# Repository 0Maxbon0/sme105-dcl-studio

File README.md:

# EscortScope — Ford Escort diagnostics by Basita

**An independent Android + ESP32 research platform for exploring legacy Ford EEC-IV diagnostics—carefully, reproducibly, and with raw evidence.**

Built around a **1998 European Ford Escort 1.6 Zetec-E** and an **EEC-IV SME-105** PCM (engineering number `97AB-12A650-KA`). The methodology, transport engineering and test tooling are intended to be useful beyond this particular vehicle.

**[Engineering brief](docs/ENGINEERING_BRIEF.md)** · [Architecture](docs/ARCHITECTURE.md) · [Hardware and components](docs/HARDWARE_GUIDE.md) · [How the code works](docs/CODE_WALKTHROUGH.md) · [Quick start](#get-started-without-a-vehicle) · [Documentation index](docs/README.md)

> [!IMPORTANT]
> **Experimental engineering project—not a certified diagnostic tool.** Network and isolated bench demonstrations do not prove vehicle-bus electrical compatibility, ECU command acceptance, sensor identities, actuator safety or road-use readiness. Do not operate the app while driving. This project is independently developed and **is not affiliated with, endorsed by or supported by Ford Motor Company**.

## Why this project exists

Many older EEC-IV vehicles have limited support in modern diagnostic ecosystems. Command formats, PID meanings and ECU calibration details can vary. A plausible-looking value is not the same as a verified sensor reading.

EscortScope, developed by Basita, is an effort to build a transparent chain from **raw bytes → timestamped capture → reproducible parser → evidence-qualified interpretation**. Rather than treating reverse-engineering hypotheses as established manufacturer specifications, each finding is labeled *Observed*, *Reference*, *Inferred* or *Unknown*.

**Identity:** an independent automotive product by Basita (بسيطة), with a steel-blue automotive action/vehicle identity, official Basita Canvas/Ink surfaces, Lagoon/Mineral selection colors, typography, spacing, controls, semantic colors and motion. See [identity and migration notes](docs/BRANDING_RELEASE.md).

### What it demonstrates

| Engineering area | Implemented work |
| --- | --- |
| **Embedded / real-time** | ESP32 UART bridge, MAX487 interface, time-bounded transmission gates, raw telemetry ring and bounded replay |
| **Android / networking** | Native Capacitor application, local-only WPA2 SoftAP, authenticated TCP, heartbeat and reconnect lifecycle; separate BLE build |
| **Data reliability** | IndexedDB raw archive, sequence-aware RX/RXB, duplicate suppression, inclusive loss reporting and crash recovery |
| **Protocol research** | Ford EEC-IV DCL experiments, Python capture tools, host simulation, and testable candidate sensor conversions |
| **Testing / engineering discipline** | Node.js, Python, JVM and PlatformIO checks, safety invariants and documented hardware-vs-simulation boundaries |

## Application preview

<table>
  <tr>
    <td align="center"></td>
    <td align="center"></td>
  </tr>
  <tr><td align="center"><sub>Live telemetry view</sub></td><td align="center"><sub>Captured-data replay view</sub></td></tr>
</table>

*These are historical application screenshots, not a claim that the latest build or every displayed sensor mapping has been validated on a vehicle.*

## Current engineering status

**Current release (26 November 2026):** Android **v2.2.1** (build **31**) and ESP32 firmware **v30**. EscortScope was installed in place on a Samsung Galaxy A52s; the original package identity and saved recordings were retained. The compact live dashboard exposes readings earlier and offers direct data-set selection. All application select lists now use the branded choice sheet; saved readings use grouped dates, search and Complete/Incomplete filters. Failed and empty captures remain in the engineering archive; completion may be annotated manually without changing the diagnostic verdict. The startup screen follows actual initialization and the original Basita Unravel credit loops silently every 7.63 seconds in both themes.

**Physical bridge validation:** v30 BLE was flashed and verified by USB. With the ECU disconnected, the phone completed TX2 self-test and reached the initial DCL transmission. The former v29 BLE output reservation could never fit in its 4 KiB queue. v30 reserves a bounded report in an 8 KiB queue without bypassing electrical safety gates. Vehicle ECU response remains unverified.

**Software checks:** see the [current release notes](docs/BRANDING_RELEASE.md), [developer setup](docs/DEVELOPER_SETUP.md) and [GitHub Actions CI](.github/workflows/ci.yml). Both ESP32 profiles compiled; Android debug assembly and in-place installation passed. The earlier November 9 Wi-Fi demonstration and November 11 recovery verification remain historical observations, not current on-vehicle acceptance.

| Capability | Evidence level / limitation |
| --- | --- |
| Direct Android ↔ ESP32 Wi-Fi | **Bench demonstrated** on 9 November 2026; no router or Internet required |
| Live Data reconnect/resume | **Host-tested**; hardware RF/thermal soak and on-vehicle behavior not yet established for the new implementation |
| Recovery grace | Up to **30 s** to reconnect; not a promise of 30 s lossless telemetry |
| Telemetry history | **8,000 × 5 bytes** of raw events; ~8.3 s at a continuous 960-byte/s stream, longer at lower rates |
| EEC-IV commands, sensors and scaling | **Research in progress**; target-ECU mappings require independent confirmation |
| High-idle / VSS investigation | [Diagnostic hypotheses and validation limits](docs/high-idle-diagnosis.md), **not a confirmed ECU defect** |

A dated [physical direct-link bench report](docs/releases/2026-11-09-direct-softap-bench.md) documents the previously observed bridge connection. It must not be mistaken for field validation of the subsequent November 11 recovery changes.

## Architecture

```text
Android app (Capacitor / JavaScript / IndexedDB)
    │ Native Android Wi-Fi NetworkSpecifier + WPA2
    │ Local-only TCP :8765, session authentication
    ▼
ESP32 SoftAP (10.77.13.1 / default SSID: SME105-DIRECT-2BF8)
    │ Wi-Fi and BLE are separate firmware profiles
    │ Heartbeat, 30 s retained-session grace, bounded RX replay
    ▼
ESP32 EEC-IV DCL bridge firmware (PlatformIO, v30)
    │ USB serial for trusted provisioning and bench diagnostics
    │ Explicit per-boot TX2_BENCH + ARM/READ gates
    ▼
MAX487 electrical interface → vehicle DCL bus
    ONLY after separate electrical and procedural qualification
```

Network authentication uses an owner-entered WPA2 passphrase and its SSID-bound PBKDF2-derived session token. This is **one shared secret**, not two independent authentication factors. On Android, private credential handling uses Keystore-backed storage. No vehicle transmission occurs merely because a device connects or reconnects.

See [full architecture](docs/ARCHITECTURE.md), [Wi-Fi setup](docs/wifi_bridge_architecture_and_setup.md), [wiring and electrical safety](docs/wiring-safety.md), [code walkthrough](docs/CODE_WALKTHROUGH.md), and [firmware overview](firmware/README.md).

## Hardware — assembled bridge vs. PCB concepts

The current research bridge uses an **ESP32 DevKit-class board**, **5 V MAX487 transceiver**, receive-line **5 V → 3.3 V translation**, hardware **DE pull-down**, and USB/separately protected bench power. This is different from the **KiCad PCB R0 and compact R1** designs. R1 is a 95 × 60 mm, four-layer **review-only design** with provisional automotive power protection, regulator choices and an ESP32-WROOM-32UE module. It has **not been fabricated or vehicle-qualified**.

[Parts, GPIO map and connector caveats](docs/HARDWARE_GUIDE.md) · [KiCad design workspace](hardware/README.md) · [R1 review status](hardware/pcb-r1/REVIEW_STATUS.md)

*PCB visual is a design preview only. Passing ERC/DRC does not make a board safe to connect to an ECU.*

## Get started without a vehicle

The fastest useful evaluation is **software-only**: clone the repository, execute parsers/tests and examine the source. **You do not need an ECU, car, connected ESP32 or private diagnostic captures** for the public baseline tests (capture-dependent tests may skip).

### Requirements

- Node.js **22** and npm
- Python **3.12+** for the documented development/test environment
- Optional: JDK **21** and Android SDK for APK builds
- Optional: PlatformIO and a compatible ESP32 board for firmware development

```bash
git clone https://github.com/0Maxbon0/sme105-dcl-studio.git
cd escort-sme105-diagnostic-lab
npm ci
npm test
python -m pip install -e .
PYTHONPATH=src python -m unittest discover -s tests -q
```

Optional **compile-only** checks (no device flash):

```bash
python -m pip install -e '.[firmware]'
python -m platformio run -d firmware/sme105_usb_bridge -e esp32dev
python -m platformio run -d firmware/sme105_usb_bridge -e esp32dev_ble
```

For Android development:

```bash
npm run android:sync
cd android
./gradlew :app:testDebugUnitTest :app:assembleDebug
```

On Windows, use `gradlew.bat`. The resulting *debug* APK is at `android/app/build/outputs/apk/debug/app-debug.apk`. This README does **not** recommend connecting to the vehicle or installing experimental firmware as a first test. Provisioning and rollback are described separately in [technical setup](docs/wifi_bridge_architecture_and_setup.md).

## Repository guide

| Path | Purpose |
| --- | --- |
| [`app/`](app/) | Canonical Android WebView application and offline UI, **not** an obsolete website |
| [`android/`](android/) | Native Android plugins, transport lifecycle and JVM tests |
| [`firmware/sme105_usb_bridge/`](firmware/sme105_usb_bridge/) | ESP32 Wi-Fi/BLE builds, ring replay and hardware protection |
| [`src/ford_dcl/`](src/ford_dcl/) | Python capture and offline inspection CLI |
| [`tests/`](tests/) / [`app/tests/`](app/tests/) | Host, parser, transport and recovery regression suites |
| [`docs/`](docs/) | Guided docs index, architecture, hardware, research references, experiment logs and safety |
| [`hardware/`](hardware/) | Review-only editable KiCad PCB R0/R1 concepts, separate from the hand-wired prototype |
| [`artifacts/`](artifacts/) | Dated visual/test artifacts, **not** an APK distribution channel |
| [`captures/`](captures/) | Historical research evidence; treat raw samples as potentially sensitive |

The retired Python localhost GUI is not the supported user interface. The Android app's canonical web assets live under `app/`.

## Research integrity and safety

- **Observed** means an explicitly identified raw capture or witnessed bench/vehicle event; **Reference** means a cited external source; **Inferred** means a testable hypothesis; **Unknown** means unverified.
- A recognized command frame is **not** proof that this ECU accepts the command. A decoded PID-like number is **not** proof of its engineering units.
- There is no general arbitrary ECU-byte write API and no automatic transmit on boot, network connection or recovery. Named operations require safety gates and operator authorization. **Do not use this software as a driving aid or to deliberately reproduce an unsafe engine symptom.**
- Do not publish vehicle-identifying information, passwords, Wi-Fi tokens, NVS dumps, phone backups or sensitive recordings. Existing historical captures are preserved; see [security](SECURITY.md) for responsible reporting.

Explore the [protocol notes](docs/protocol-notes.md), [experiment plan](docs/sme105-dcl-experiment-plan-2026-11-07.md), [references](docs/REFERENCES.md) and [high-idle research](docs/high-idle-diagnosis.md).

For an overview of code internals and safe local builds, read [code walkthrough](docs/CODE_WALKTHROUGH.md) and [developer setup](docs/DEVELOPER_SETUP.md). Before sharing the repository externally, use the [publication checklist](docs/PUBLICATION_CHECKLIST.md).

## For Ford / technical reviewers

The [two-page-style engineering brief](docs/ENGINEERING_BRIEF.md) summarizes the problem, implemented architecture, verification levels, unanswered questions and specific requests for historical EEC-IV documentation or calibration information. The project's intent is to improve maintainability and safe understanding of a legacy vehicle, **not** to imply access to or endorsement by Ford engineering.

## Contributing, security and licensing

Reports should include the exact ECU and firmware/app versions, transport mode, safety state, original capture identifier, clock settings, digest and reproduction steps. Keep identifying raw captures private. See the [wiring and electrical safety guide](docs/wiring-safety.md).

Contributions to parsers, tests, documentation and evidence-based research are welcome. Please read [CONTRIBUTING.md](CONTRIBUTING.md) and [SECURITY.md](SECURITY.md) before sharing files or proposing active hardware experiments.

**License status:** This repository is **publicly viewable but not currently open-source licensed**. Public access alone does not grant reuse, modification or redistribution rights. The maintainer must deliberately select and add a license before describing the code as open source.

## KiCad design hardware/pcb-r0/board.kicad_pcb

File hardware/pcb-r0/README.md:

# SME105 DCL Bridge — PCB R0 engineering prototype

**State:** editable KiCad schematic and four-layer PCB now routed with ground planes. Prototype-review **only**: NOT vehicle-qualified, NOT manufacturing approved. See `REVIEW_STATUS.md`.
**Source reviewed:** firmware/sme105_usb_bridge/README.md and platformio.ini; docs/wiring-safety.md, docs/max487-quickstart.md and docs/wifi_ble_stability_and_rf_report.md.
**Scope:** single-board replacement for current ESP32 DevKit + MAX487 + RO 5V-to-3.3V translation; retain the existing GPIO map and firmware. Add protected OBD power and optional external 2.4 GHz antenna. No new Bluetooth chipset needed.

## Electrical architecture — proposed

```text
OBD verified pigtail (J1 header placeholder)  Automotive protection/power
  pin 16 VBAT --- fuse --- reverse-polarity stage --- surge clamp
                                                  |
                                   automotive buck 5V (candidate LM5164-Q1)
                                     |                       |
                                 MAX487 VCC              3V3 regulator
                                     |                       |
OBD pin 3?  -------- DNP link -- A/B?                     ESP32-WROOM-32UE-N4
OBD pin 11? -------- DNP link -- B/A?                       | BLE + Wi-Fi integrated
                                     |                        +-- IPEX 2.4 GHz antenna
                            MAX487 RO -- resistor divider --> GPIO16
                            MAX487 DI <------------------------ GPIO17
                            MAX487 DE <------------------------ GPIO18
                                   + 10k pull-down to GND
                            MAX487 /RE --> GND (receiver enabled)
OBD pin 4 --> GND; pin 5 --> reference-isolation DNP link; verify on car
UART programming/service header: 3V3/GND/TXD0/RXD0/EN/GPIO0 (and optional USB/UART debug adapter)
OBD pin 7 IS NOT DCL; leave unconnected in R0.
```

## Reused firmware signals (confirmed from source)

| Logic | ESP32 GPIO | WROOM-32UE pad | Direction | Other end |
|---|---:|---:|---|---|
| DCL RX | 16 | 27 | IN | MAX487 RO through 5V->3V3 conversion |
| DCL TX | 17 | 28 | OUT and pad witness | MAX487 DI |
| Driver enable | 18 | 30 | OUT | MAX487 DE and 10k resistor to GND |
| Enable receiver | — | — | — | MAX487 /RE tied to GND |
| UART flashing | TXD0/RXD0 | 35/34 | IO | service header; no DevKit USB-UART required |

## Core choices

1. **ESP32-WROOM-32UE-N4** rather than the complete DevKit. The classic ESP32 core retains the GPIO/UART architecture used by the repository; N4 has 4 MB flash. The UE version includes an RF connector for a *suitable* approved 2.4 GHz antenna.
2. **No second Bluetooth module:** current firmware already contains optional NimBLE UART transport (build flag `SME105_BLE`); deployed Wi-Fi image is a different configuration. Improve radio by antenna placement/measurements, not a second radio by assumption.
3. **Keep the existing MAX487 functional interface for R0.** A 3.3V-native replacement could eliminate the 5V RX translator, but changes the bus electrical interface and requires validation against the actual DCL wiring.
4. **Input power is a fresh engineering subsystem, not the old bench wiring.** 12V OBD pin 16 must never connect directly to ESP32/5V/3V3 rails. Proposed protection chain and a 6–100 V-rated automotive buck are preliminary; final reverse polarity, surge/load-dump, fuse, thermal and sleep-current design must be calculated and tested before vehicle power-on.
5. **No assumption that pins 3/11 A/B or 120-ohm termination are correct** until measured on this specific SME-105 ECU and connector.
6. Boot hardware must hold DE OFF regardless of ESP boot state. Reserve access for programming/debugging even after removing the DevKit.

## Suggested PCB zones (mechanical dimensions NOT final)

- **Vehicle-facing edge:** OBD connector, fuse/reverse-polarity/surge input, DCL protection.
- **Center:** 5V/3V3 switching supply, MAX487, RO divider.
- **Antenna edge:** WROOM-32UE with connector and RF clearance; antenna routed away from car metal and switching inductor.
- **Service:** test pads + UART firmware recovery header + optional physical disconnect/disable for bus driver.
- Board shape depends on the exact OBD male connector and case. Do **not** commit to dimensions or component footprints without the mechanical part numbers.

## Release gates (before CAD manufacturing exports)

- Confirm current physical module identity, 5V logic shifter board and MAX487 part/variant; record photographs of both sides.
- Verify exact OBD connector pins and GND, especially DCL 3/11 polarity and actual bus load, on this car.
- Choose direct-plug or short-cable OBD male connector and enclosure dimensions.
- Complete KiCad GUI ERC, resolve 0.20 mm thermal drill feasibility and review PCB copper and antenna layout with real module and manufacturer constraints.
- Validate automotive power path (reverse polarity, cranking, load dump/transients, peak Wi-Fi/BLE current, ignition-off parasitic drain).
- Compare USB-only bench functional signals and active-driver safety with existing bridge; field ECU operation is a separate approval.
- Compile and verify matching Wi-Fi and BLE profiles on the replacement module without altering saved app/device settings unexpectedly.

## Primary component references

- Espressif ESP32-WROOM-32E/32UE datasheet: https://documentation.espressif.com/esp32-wroom-32e_esp32-wroom-32ue_datasheet_en.html
- Espressif ESP32 hardware schematic checklist: https://docs.espressif.com/projects/esp-hardware-design-guidelines/en/latest/esp32/schematic-checklist.html
- TI LM5164-Q1 candidate regulator: https://www.ti.com/product/LM5164-Q1
- KiCad: https://www.kicad.org/

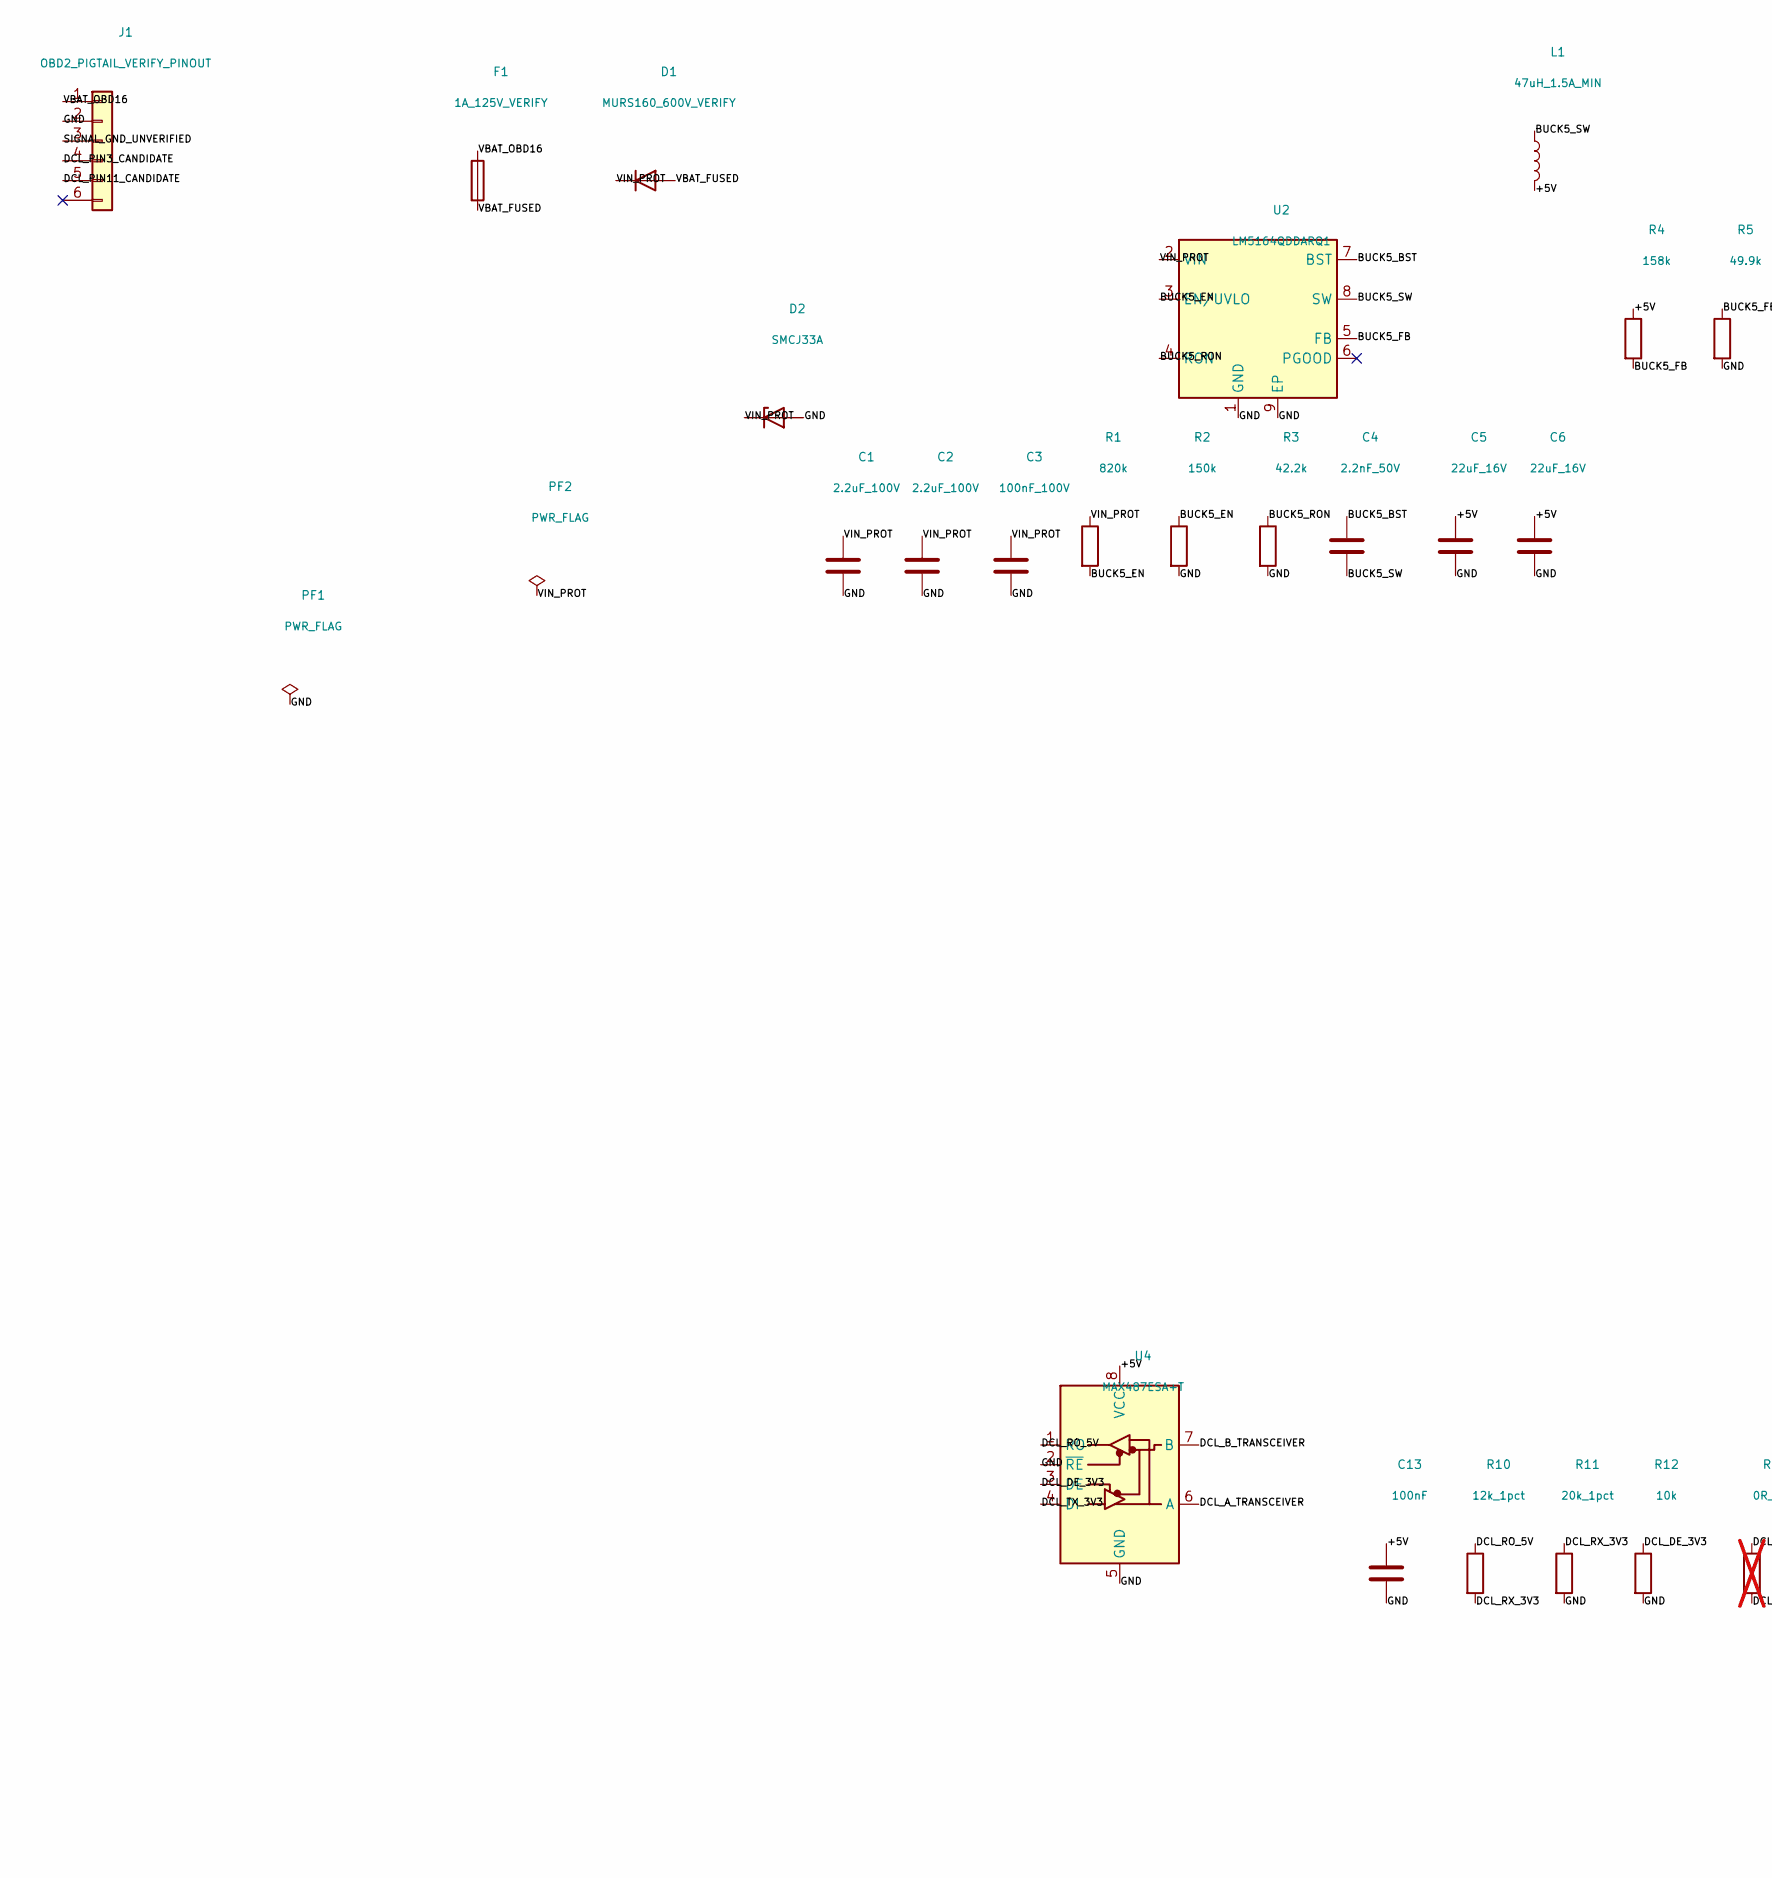
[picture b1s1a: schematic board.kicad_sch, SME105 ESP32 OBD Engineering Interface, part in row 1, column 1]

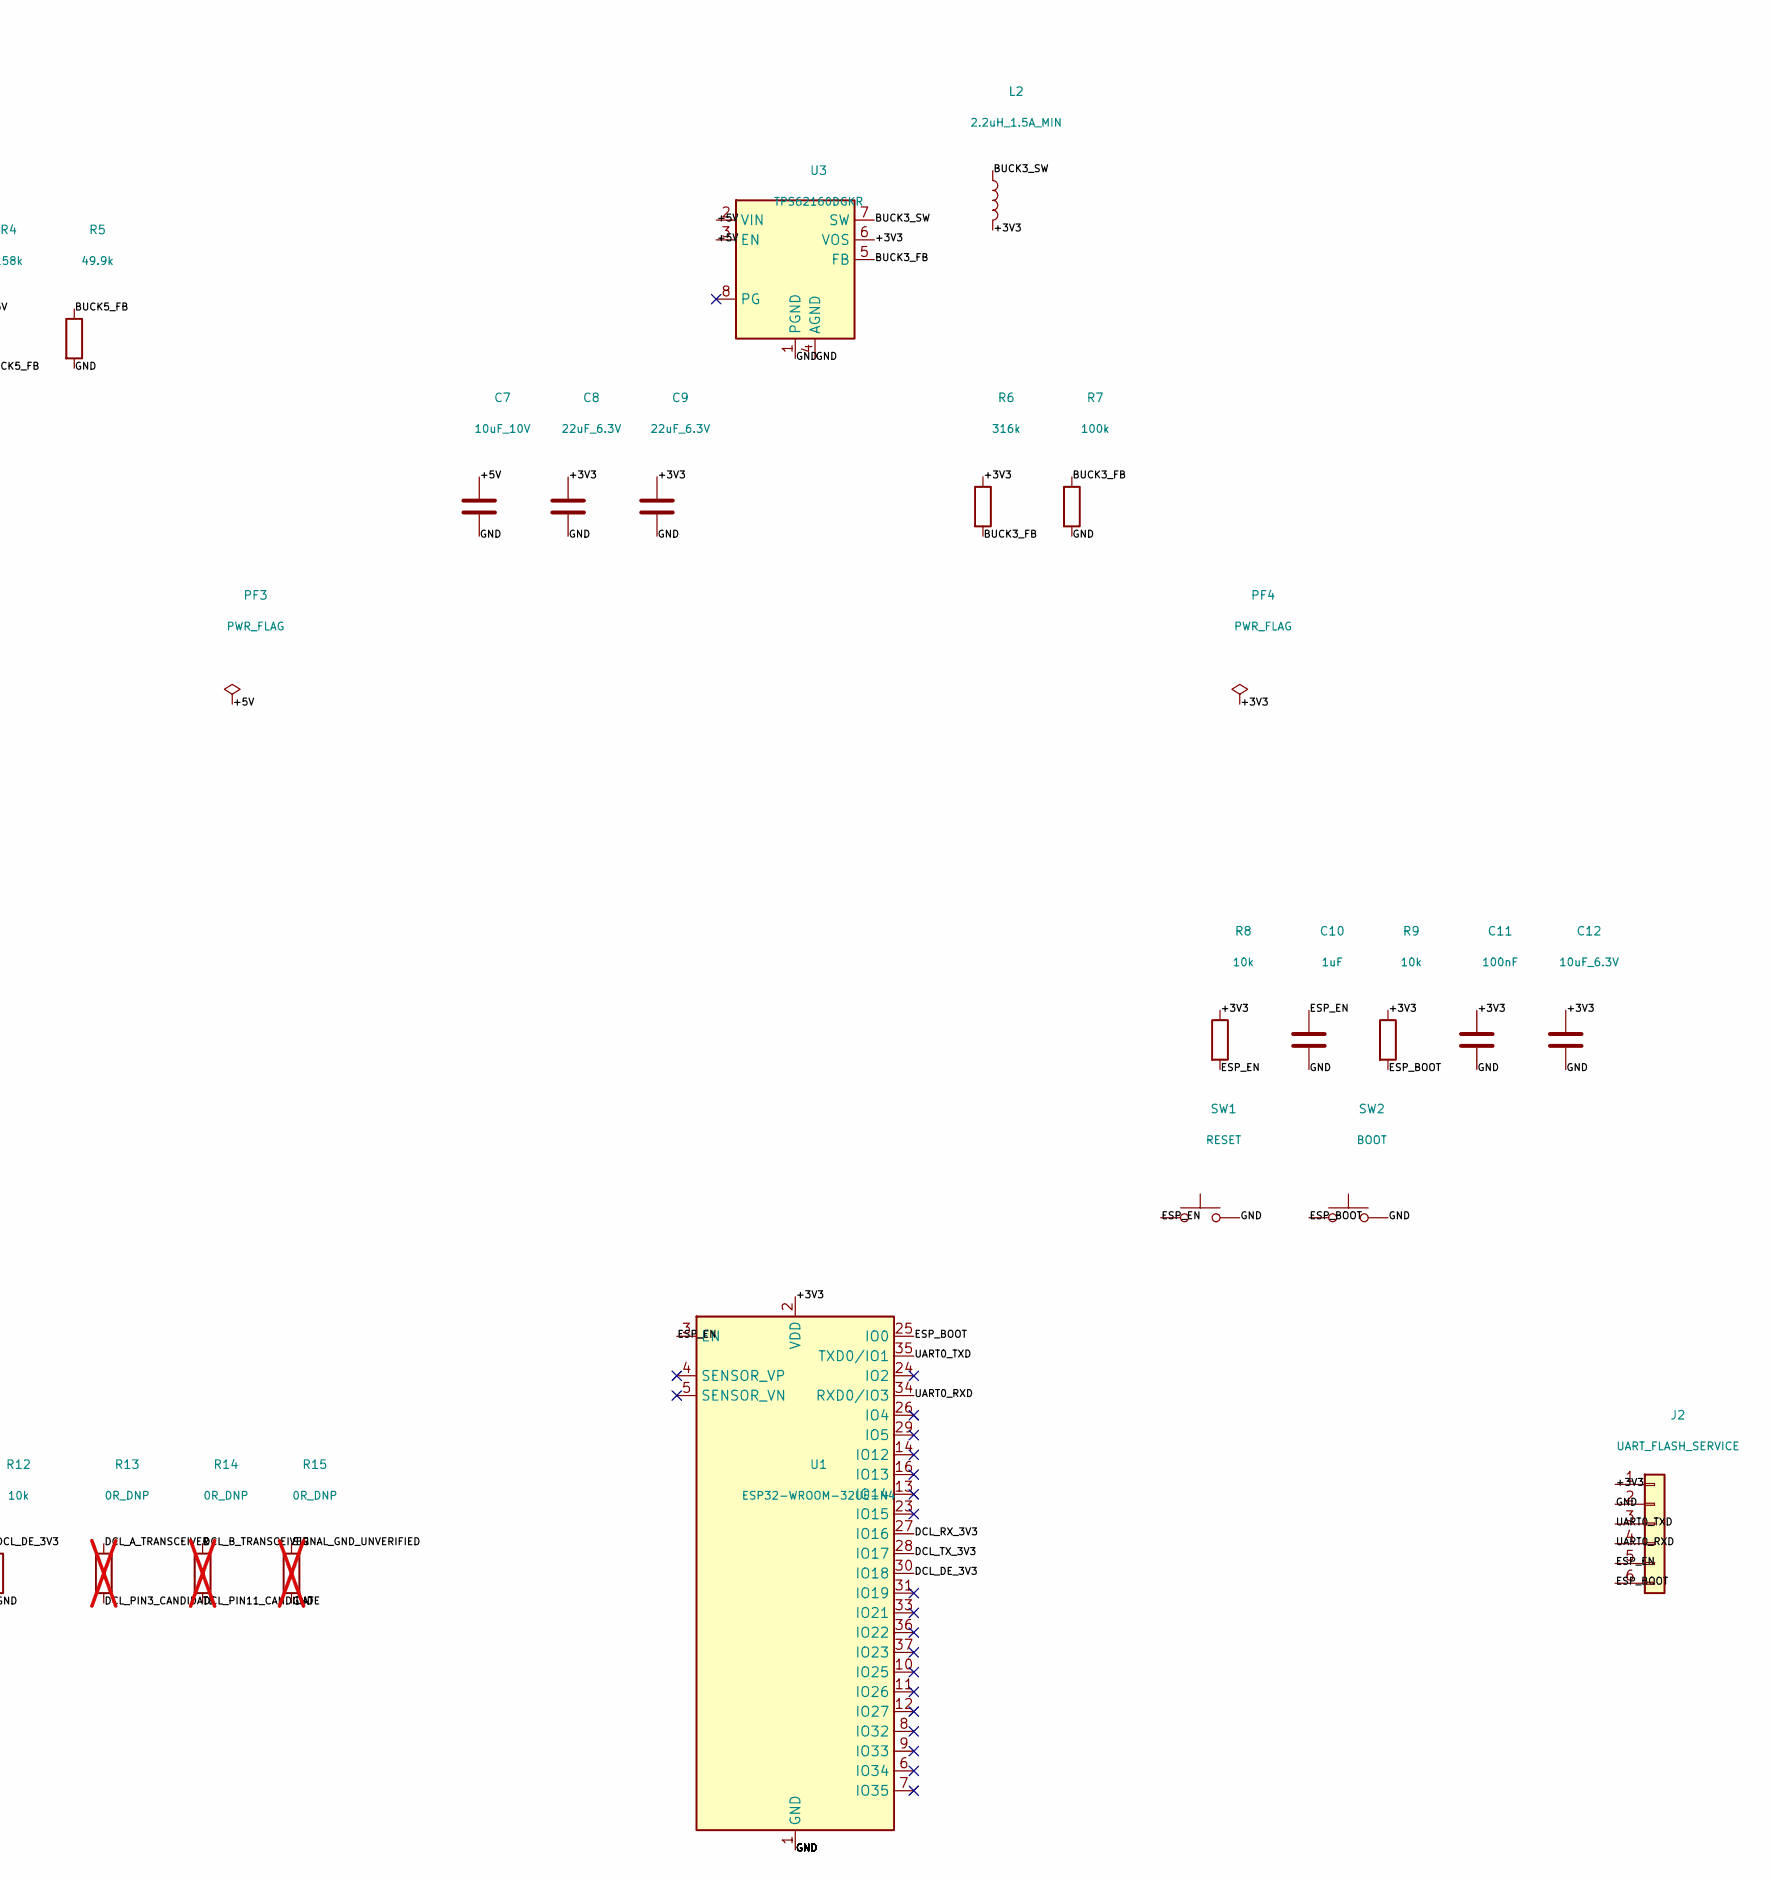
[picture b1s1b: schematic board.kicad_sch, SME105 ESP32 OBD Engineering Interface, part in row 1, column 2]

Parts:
C1, C2: 2.2uF_100V; Capacitor_SMD__C_1210_3225Metric
C3: 100nF_100V; Capacitor_SMD__C_0805_2012Metric
C4: 2.2nF_50V; Capacitor_SMD__C_0603_1608Metric
C5, C6: 22uF_16V; Capacitor_SMD__C_1206_3216Metric
C7: 10uF_10V; Capacitor_SMD__C_1206_3216Metric
C8, C9: 22uF_6.3V; Capacitor_SMD__C_1206_3216Metric
C10: 1uF; Capacitor_SMD__C_0603_1608Metric
C11, C13: 100nF; Capacitor_SMD__C_0603_1608Metric
C12: 10uF_6.3V; Capacitor_SMD__C_1206_3216Metric
D1: MURS160_600V_VERIFY; Diode_SMD__D_SMB
D2: SMCJ33A; Diode_SMD__D_SMC
F1: 1A_125V_VERIFY; Fuse__Fuse_2512_6332Metric
J1: OBD2_PIGTAIL_VERIFY_PINOUT; Connector_PinHeader_2.54mm__PinHeader_1x06_P2.54mm_Vertical
J2: UART_FLASH_SERVICE; Connector_PinHeader_2.54mm__PinHeader_1x06_P2.54mm_Vertical
L1: 47uH_1.5A_MIN; Inductor_SMD__L_10.4x10.4_H4.8
L2: 2.2uH_1.5A_MIN; Inductor_SMD__L_Taiyo-Yuden_NR-50xx
PF1, PF2, PF3, PF4: PWR_FLAG
R1: 820k; Resistor_SMD__R_0603_1608Metric
R2: 150k; Resistor_SMD__R_0603_1608Metric
R3: 42.2k; Resistor_SMD__R_0603_1608Metric
R4: 158k; Resistor_SMD__R_0603_1608Metric
R5: 49.9k; Resistor_SMD__R_0603_1608Metric
R6: 316k; Resistor_SMD__R_0603_1608Metric
R7: 100k; Resistor_SMD__R_0603_1608Metric
R8, R9, R12: 10k; Resistor_SMD__R_0603_1608Metric
R10: 12k_1pct; Resistor_SMD__R_0603_1608Metric
R11: 20k_1pct; Resistor_SMD__R_0603_1608Metric
R13, R14, R15: 0R_DNP; Resistor_SMD__R_0805_2012Metric; not fitted
SW1: RESET; Button_Switch_SMD__SW_SPST_B3U-1000P
SW2: BOOT; Button_Switch_SMD__SW_SPST_B3U-1000P
U1: ESP32-WROOM-32UE-N4; RF_Module__ESP32-WROOM-32UE; MPN ESP32-WROOM-32UE-N4
U2: LM5164QDDARQ1; Package_SO__HSOP-8-1EP_3.9x4.9mm_P1.27mm_EP2.41x3.1mm_Therm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; MPN LM5164QDDARQ1
U3: TPS62160DGKR; Package_SO__MSOP-8_3x3mm_P0.65mm; MPN TPS62160DGKR
U4: MAX487ESA+T; Package_SO__SOIC-8_3.9x4.9mm_P1.27mm; MPN MAX487ESA+T

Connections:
+3V3: C8.1, C9.1, C11.1, C12.1, J2.1, L2.2, PF4.1, R6.1, R8.1, R9.1, U1.2 (VDD), U3.6 (VOS)
+5V: C5.1, C6.1, C7.1, C13.1, L1.2, PF3.1, R4.1, U3.2 (VIN), U3.3 (EN), U4.8 (VCC)
BUCK3_FB: R6.2, R7.1, U3.5 (FB)
BUCK3_SW: L2.1, U3.7 (SW)
BUCK5_BST: C4.1, U2.7 (BST)
BUCK5_EN: R1.2, R2.1, U2.3 (EN/UVLO)
BUCK5_FB: R4.2, R5.1, U2.5 (FB)
BUCK5_RON: R3.1, U2.4 (RON)
BUCK5_SW: C4.2, L1.1, U2.8 (SW)
DCL_A_TRANSCEIVER: R13.1, U4.6 (A)
DCL_B_TRANSCEIVER: R14.1, U4.7 (B)
DCL_DE_3V3: R12.1, U1.30 (IO18), U4.3 (DE)
DCL_PIN3_CANDIDATE: J1.4, R13.2
DCL_PIN11_CANDIDATE: J1.5, R14.2
DCL_RO_5V: R10.1, U4.1 (RO)
DCL_RX_3V3: R10.2, R11.1, U1.27 (IO16)
DCL_TX_3V3: U1.28 (IO17), U4.4 (DI)
ESP_BOOT: J2.6, R9.2, SW2.1, U1.25 (IO0)
ESP_EN: C10.1, J2.5, R8.2, SW1.1, U1.3 (EN)
GND: C1.2, C2.2, C3.2, C5.2, C6.2, C7.2, C8.2, C9.2, C10.2, C11.2, C12.2, C13.2, D2.2 (A), J1.2, J2.2, PF1.1, R2.2, R3.2, R5.2, R7.2, R11.2, R12.2, R15.2, SW1.2, SW2.2, U1.1 (GND), U1.15 (GND), U1.38 (GND), U1.39 (GND), U2.1 (GND), U2.9 (EP), U3.1 (PGND), U3.4 (AGND), U4.2 (~RE), U4.5 (GND)
SIGNAL_GND_UNVERIFIED: J1.3, R15.1
UART0_RXD: J2.4, U1.34 (RXD0/IO3)
UART0_TXD: J2.3, U1.35 (TXD0/IO1)
VBAT_FUSED: D1.2 (A), F1.2
VBAT_OBD16: F1.1, J1.1
VIN_PROT: C1.1, C2.1, C3.1, D1.1 (K), D2.1 (K), PF2.1, R1.1, U2.2 (VIN)

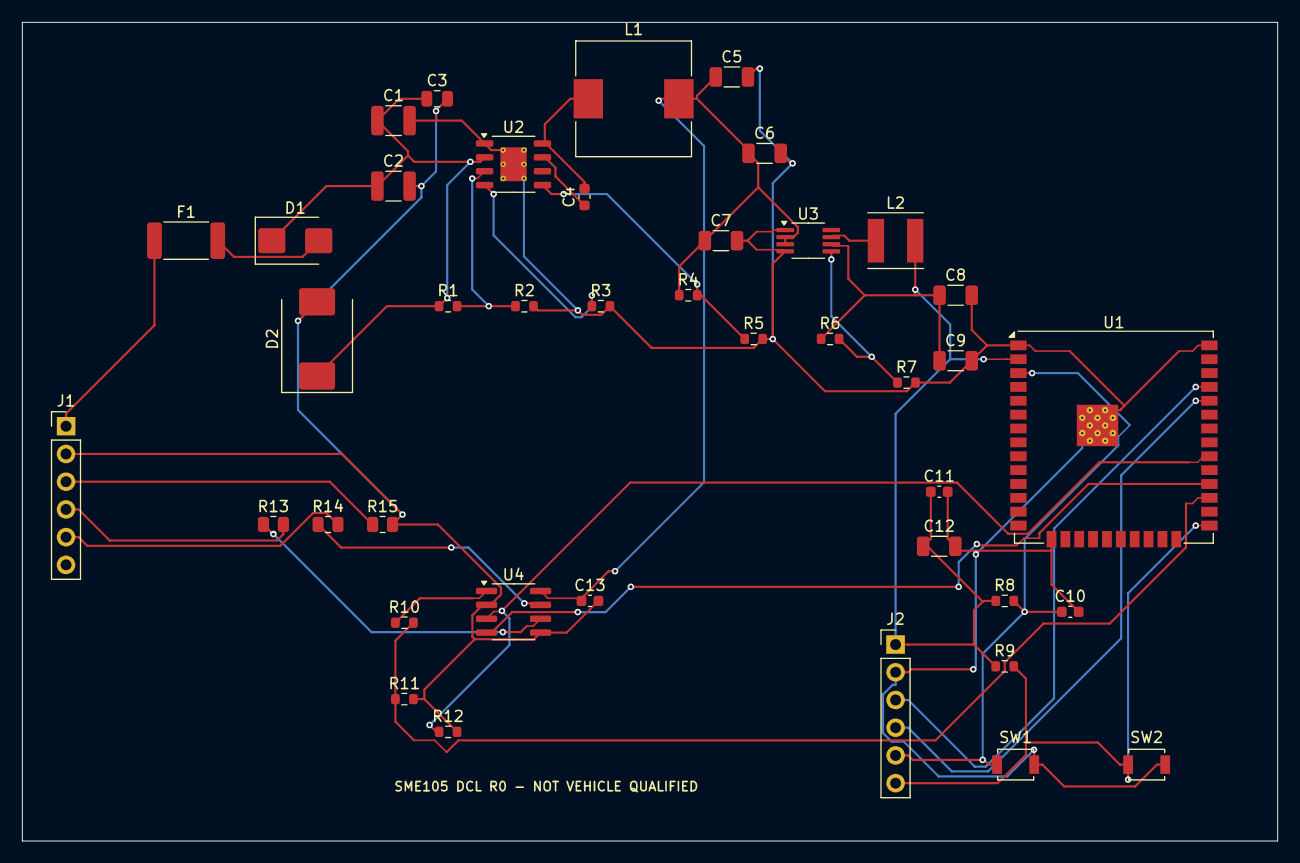
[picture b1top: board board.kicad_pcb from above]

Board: 4 copper layers, 115.0 x 75.0 mm, 41 parts (0 on the bottom side), 26 nets.

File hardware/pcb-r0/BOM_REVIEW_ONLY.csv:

Ref,Qty,Value,Footprint,MPN,Assembly,Status
C1,1,2.2uF_100V,SME105:Capacitor_SMD__C_1210_3225Metric,,PROVISIONAL / VERIFY,ENGINEERING CHOICE - ORDERABLE PART NOT SELECTED
C10,1,1uF,SME105:Capacitor_SMD__C_0603_1608Metric,,PROVISIONAL / VERIFY,ENGINEERING CHOICE - ORDERABLE PART NOT SELECTED
C11,1,100nF,SME105:Capacitor_SMD__C_0603_1608Metric,,PROVISIONAL / VERIFY,ENGINEERING CHOICE - ORDERABLE PART NOT SELECTED
C12,1,10uF_6.3V,SME105:Capacitor_SMD__C_1206_3216Metric,,PROVISIONAL / VERIFY,ENGINEERING CHOICE - ORDERABLE PART NOT SELECTED
C13,1,100nF,SME105:Capacitor_SMD__C_0603_1608Metric,,PROVISIONAL / VERIFY,ENGINEERING CHOICE - ORDERABLE PART NOT SELECTED
C2,1,2.2uF_100V,SME105:Capacitor_SMD__C_1210_3225Metric,,PROVISIONAL / VERIFY,ENGINEERING CHOICE - ORDERABLE PART NOT SELECTED
C3,1,100nF_100V,SME105:Capacitor_SMD__C_0805_2012Metric,,PROVISIONAL / VERIFY,ENGINEERING CHOICE - ORDERABLE PART NOT SELECTED
C4,1,2.2nF_50V,SME105:Capacitor_SMD__C_0603_1608Metric,,PROVISIONAL / VERIFY,ENGINEERING CHOICE - ORDERABLE PART NOT SELECTED
C5,1,22uF_16V,SME105:Capacitor_SMD__C_1206_3216Metric,,PROVISIONAL / VERIFY,ENGINEERING CHOICE - ORDERABLE PART NOT SELECTED
C6,1,22uF_16V,SME105:Capacitor_SMD__C_1206_3216Metric,,PROVISIONAL / VERIFY,ENGINEERING CHOICE - ORDERABLE PART NOT SELECTED
C7,1,10uF_10V,SME105:Capacitor_SMD__C_1206_3216Metric,,PROVISIONAL / VERIFY,ENGINEERING CHOICE - ORDERABLE PART NOT SELECTED
C8,1,22uF_6.3V,SME105:Capacitor_SMD__C_1206_3216Metric,,PROVISIONAL / VERIFY,ENGINEERING CHOICE - ORDERABLE PART NOT SELECTED
C9,1,22uF_6.3V,SME105:Capacitor_SMD__C_1206_3216Metric,,PROVISIONAL / VERIFY,ENGINEERING CHOICE - ORDERABLE PART NOT SELECTED
D1,1,MURS160_600V_VERIFY,SME105:Diode_SMD__D_SMB,,PROVISIONAL / VERIFY,ENGINEERING CHOICE - ORDERABLE PART NOT SELECTED
D2,1,SMCJ33A,SME105:Diode_SMD__D_SMC,,PROVISIONAL / VERIFY,ENGINEERING CHOICE - ORDERABLE PART NOT SELECTED
F1,1,1A_125V_VERIFY,SME105:Fuse__Fuse_2512_6332Metric,,PROVISIONAL / VERIFY,ENGINEERING CHOICE - ORDERABLE PART NOT SELECTED
J1,1,OBD2_PIGTAIL_VERIFY_PINOUT,SME105:Connector_PinHeader_2.54mm__PinHeader_1x06_P2.54mm_Vertical,,PROVISIONAL / VERIFY,ENGINEERING CHOICE - ORDERABLE PART NOT SELECTED
J2,1,UART_FLASH_SERVICE,SME105:Connector_PinHeader_2.54mm__PinHeader_1x06_P2.54mm_Vertical,,PROVISIONAL / VERIFY,ENGINEERING CHOICE - ORDERABLE PART NOT SELECTED
L1,1,47uH_1.5A_MIN,SME105:Inductor_SMD__L_10.4x10.4_H4.8,,PROVISIONAL / VERIFY,ENGINEERING CHOICE - ORDERABLE PART NOT SELECTED
L2,1,2.2uH_1.5A_MIN,SME105:Inductor_SMD__L_Taiyo-Yuden_NR-50xx,,PROVISIONAL / VERIFY,ENGINEERING CHOICE - ORDERABLE PART NOT SELECTED
R1,1,820k,SME105:Resistor_SMD__R_0603_1608Metric,,PROVISIONAL / VERIFY,ENGINEERING CHOICE - ORDERABLE PART NOT SELECTED
R10,1,12k_1pct,SME105:Resistor_SMD__R_0603_1608Metric,,PROVISIONAL / VERIFY,ENGINEERING CHOICE - ORDERABLE PART NOT SELECTED
R11,1,20k_1pct,SME105:Resistor_SMD__R_0603_1608Metric,,PROVISIONAL / VERIFY,ENGINEERING CHOICE - ORDERABLE PART NOT SELECTED
R12,1,10k,SME105:Resistor_SMD__R_0603_1608Metric,,PROVISIONAL / VERIFY,ENGINEERING CHOICE - ORDERABLE PART NOT SELECTED
R13,1,0R_DNP,SME105:Resistor_SMD__R_0805_2012Metric,,DO NOT POPULATE,ENGINEERING CHOICE - ORDERABLE PART NOT SELECTED
R14,1,0R_DNP,SME105:Resistor_SMD__R_0805_2012Metric,,DO NOT POPULATE,ENGINEERING CHOICE - ORDERABLE PART NOT SELECTED
R15,1,0R_DNP,SME105:Resistor_SMD__R_0805_2012Metric,,DO NOT POPULATE,ENGINEERING CHOICE - ORDERABLE PART NOT SELECTED
R2,1,150k,SME105:Resistor_SMD__R_0603_1608Metric,,PROVISIONAL / VERIFY,ENGINEERING CHOICE - ORDERABLE PART NOT SELECTED
R3,1,42.2k,SME105:Resistor_SMD__R_0603_1608Metric,,PROVISIONAL / VERIFY,ENGINEERING CHOICE - ORDERABLE PART NOT SELECTED
R4,1,158k,SME105:Resistor_SMD__R_0603_1608Metric,,PROVISIONAL / VERIFY,ENGINEERING CHOICE - ORDERABLE PART NOT SELECTED
R5,1,49.9k,SME105:Resistor_SMD__R_0603_1608Metric,,PROVISIONAL / VERIFY,ENGINEERING CHOICE - ORDERABLE PART NOT SELECTED
R6,1,316k,SME105:Resistor_SMD__R_0603_1608Metric,,PROVISIONAL / VERIFY,ENGINEERING CHOICE - ORDERABLE PART NOT SELECTED
R7,1,100k,SME105:Resistor_SMD__R_0603_1608Metric,,PROVISIONAL / VERIFY,ENGINEERING CHOICE - ORDERABLE PART NOT SELECTED
R8,1,10k,SME105:Resistor_SMD__R_0603_1608Metric,,PROVISIONAL / VERIFY,ENGINEERING CHOICE - ORDERABLE PART NOT SELECTED
R9,1,10k,SME105:Resistor_SMD__R_0603_1608Metric,,PROVISIONAL / VERIFY,ENGINEERING CHOICE - ORDERABLE PART NOT SELECTED
SW1,1,RESET,SME105:Button_Switch_SMD__SW_SPST_B3U-1000P,,PROVISIONAL / VERIFY,ENGINEERING CHOICE - ORDERABLE PART NOT SELECTED
SW2,1,BOOT,SME105:Button_Switch_SMD__SW_SPST_B3U-1000P,,PROVISIONAL / VERIFY,ENGINEERING CHOICE - ORDERABLE PART NOT SELECTED
U1,1,ESP32-WROOM-32UE-N4,SME105:RF_Module__ESP32-WROOM-32UE,ESP32-WROOM-32UE-N4,PROVISIONAL / VERIFY,EXACT MPN RECORDED; VERIFY AVAILABILITY
U2,1,LM5164QDDARQ1,SME105:Package_SO__HSOP-8-1EP_3.9x4.9mm_P1.27mm_EP2.41x3.1mm_ThermalVias,LM5164QDDARQ1,PROVISIONAL / VERIFY,EXACT MPN RECORDED; VERIFY AVAILABILITY
U3,1,TPS62160DGKR,SME105:Package_SO__MSOP-8_3x3mm_P0.65mm,TPS62160DGKR,PROVISIONAL / VERIFY,EXACT MPN RECORDED; VERIFY AVAILABILITY
U4,1,MAX487ESA+T,SME105:Package_SO__SOIC-8_3.9x4.9mm_P1.27mm,MAX487ESA+T,PROVISIONAL / VERIFY,EXACT MPN RECORDED; VERIFY AVAILABILITY

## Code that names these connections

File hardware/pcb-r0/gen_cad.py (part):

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# The OBD cable remains an externally supplied VERIFIED pigtail.
# No direct plug footprint is invented before its supplier/mechanical choice.
add("J1","Connector_Generic","Conn_01x06","OBD2_PIGTAIL_VERIFY_PINOUT",F_J,
    {1:"VBAT_OBD16",2:"GND",3:"SIGNAL_GND_UNVERIFIED",4:"DCL_PIN3_CANDIDATE",5:"DCL_PIN11_CANDIDATE"},39,60)
add("F1","Device","Fuse","1A_125V_VERIFY", "Fuse:Fuse_2512_6332Metric",
    {1:"VBAT_OBD16",2:"VBAT_FUSED"},88,65)
add("D1","Device","D","MURS160_600V_VERIFY","Diode_SMD:D_SMB",
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add("R11","Device","R","20k_1pct",F_R,{1:"DCL_RX_3V3",2:"GND"},227,244)
add("R12","Device","R","10k",F_R,{1:"DCL_DE_3V3",2:"GND"},238,244)
add("R13","Device","R","0R_DNP","Resistor_SMD:R_0805_2012Metric",
    {1:"DCL_A_TRANSCEIVER",2:"DCL_PIN3_CANDIDATE"},251,244,dnp=True)
add("R14","Device","R","0R_DNP","Resistor_SMD:R_0805_2012Metric",
    {1:"DCL_B_TRANSCEIVER",2:"DCL_PIN11_CANDIDATE"},264,244,dnp=True)
add("R15","Device","R","0R_DNP","Resistor_SMD:R_0805_2012Metric",
    {1:"SIGNAL_GND_UNVERIFIED",2:"GND"},275,244,dnp=True)

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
